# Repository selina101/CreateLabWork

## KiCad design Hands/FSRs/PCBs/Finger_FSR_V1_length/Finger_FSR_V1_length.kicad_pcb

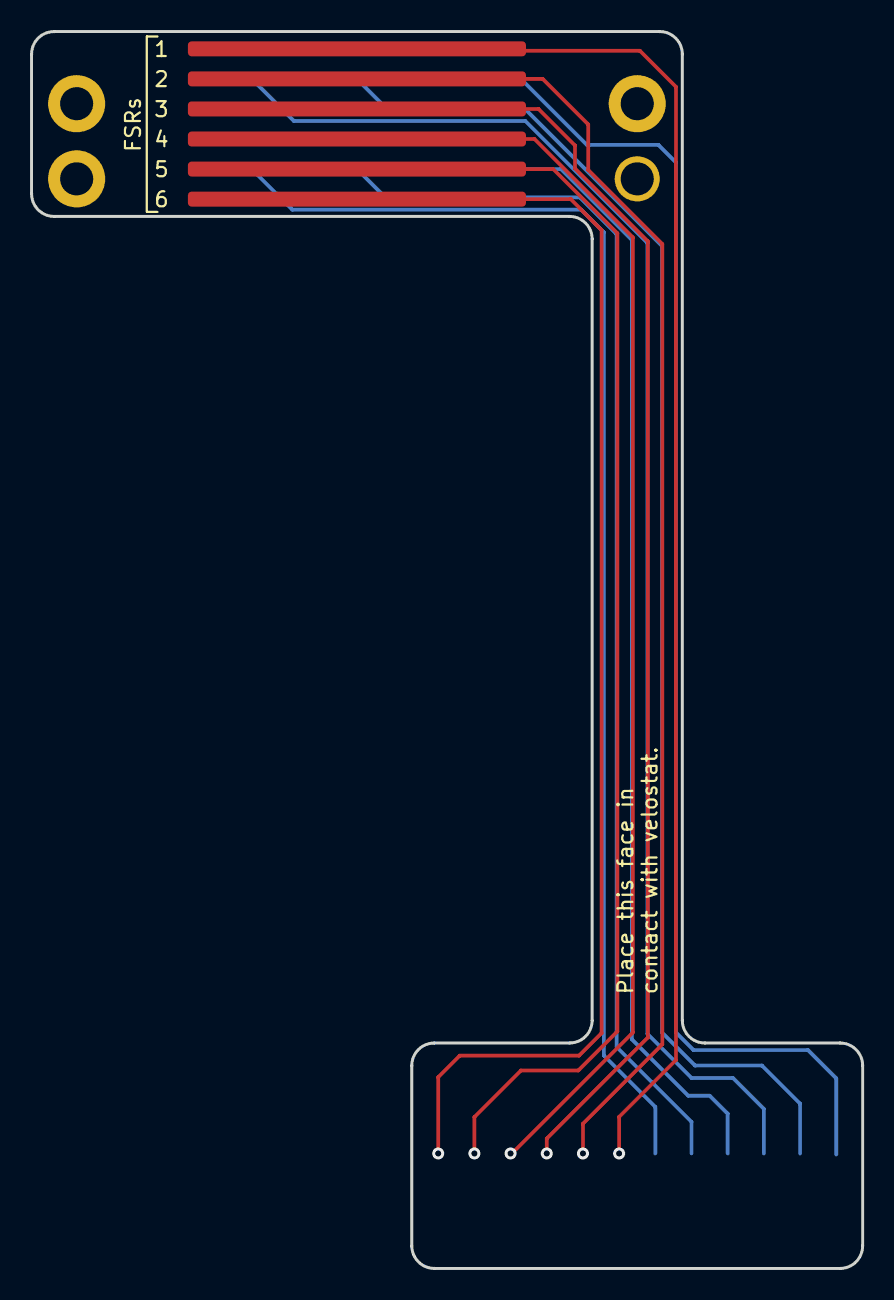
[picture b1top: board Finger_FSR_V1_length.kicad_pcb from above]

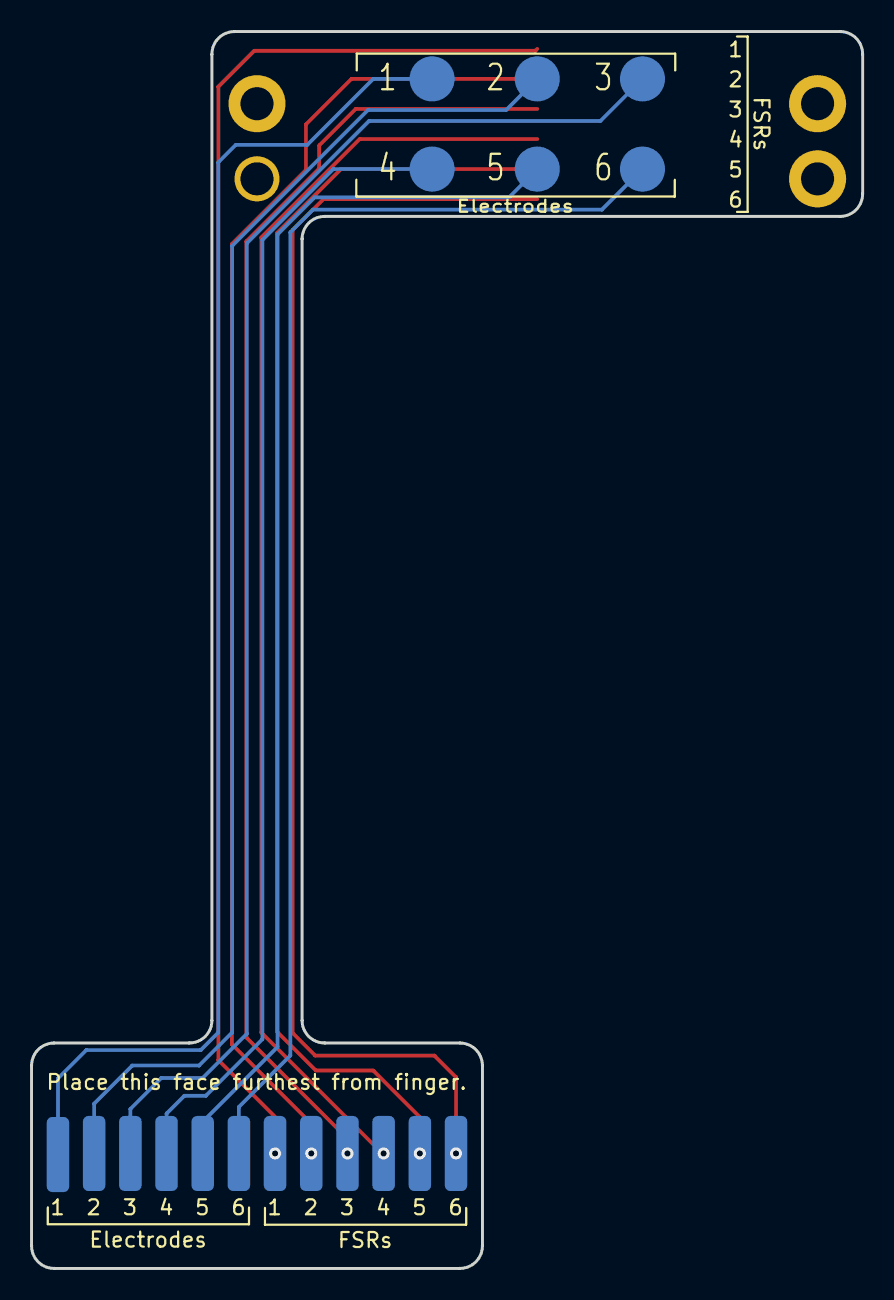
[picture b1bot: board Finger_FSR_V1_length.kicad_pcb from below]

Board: 2 copper layers, 55.3 x 82.3 mm, 28 parts (18 on the bottom side), 12 nets.

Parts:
E1, E2, E3, E4, E5, E6: Finger_FSR_V1_Length
E7, E8, E9, E10, E11, E12: Electrode
H1, H2, H3, H4: MountingHole_Pad; MountingHole_2.2mm_M2_DIN965_Pad
U1, U2, U3, U4, U5, U6: pad
U7, U8, U9, U10, U11, U12: pad; Long_pad

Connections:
unnamed: E1.1, U1.1
unnamed: E2.1, U2.1
unnamed: E3.1, U3.1
unnamed: E4.1, U4.1
unnamed: E5.1, U5.1
unnamed: E6.1, U6.1
unnamed: E7.1, U7.1
unnamed: E8.1, U8.1
unnamed: E9.1, U9.1
unnamed: E10.1, U10.1
unnamed: E11.1, U11.1
unnamed: E12.1, U12.1

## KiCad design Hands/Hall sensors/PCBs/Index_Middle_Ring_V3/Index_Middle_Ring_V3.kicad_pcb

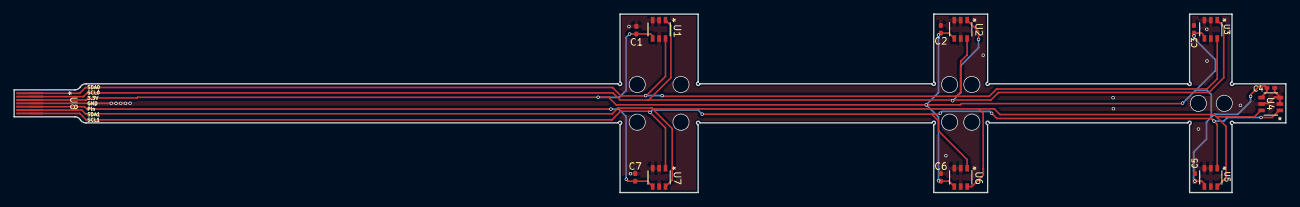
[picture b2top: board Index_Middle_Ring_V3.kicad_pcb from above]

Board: 2 copper layers, 188.9 x 26.5 mm, 15 parts (0 on the bottom side), 7 nets.

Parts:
C1, C2, C3, C4, C5, C6, C7: 0.1uF; C_0402_1005Metric_Pad0.74x0.62mm_HandSolder
U1, U2, U3, U4, U5, U6, U7: TMAG5273A2QDBVR; TMAG5273A2
U8: 7Pin_FingerConnector_for 0527450797

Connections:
+3V3: C1.1, C2.1, C3.1, C4.1, C5.1, C6.1, U1.4 (VCC), U2.4 (VCC), U3.4 (VCC), U4.4 (VCC), U5.4 (VCC), U6.4 (VCC), U8.3
/Pin: C7.1, U7.4 (VCC), U8.5
/SCL0: U1.1 (SCL), U2.1 (SCL), U3.1 (SCL), U8.2
/SCL1: U4.1 (SCL), U5.1 (SCL), U6.1 (SCL), U7.1 (SCL), U8.7
/SDA0: U1.6 (SDA), U2.6 (SDA), U3.6 (SDA), U8.1
/SDA1: U4.6 (SDA), U5.6 (SDA), U6.6 (SDA), U7.6 (SDA), U8.6
GND: C1.2, C2.2, C3.2, C4.2, C5.2, C6.2, C7.2, U1.2 (GND), U1.3 (GND(TEST)), U1.5 (*INT), U2.2 (GND), U2.3 (GND(TEST)), U2.5 (*INT), U3.2 (GND), U3.3 (GND(TEST)), U3.5 (*INT), U4.2 (GND), U4.3 (GND(TEST)), U4.5 (*INT), U5.2 (GND), U5.3 (GND(TEST)), U5.5 (*INT), U6.2 (GND), U6.3 (GND(TEST)), U6.5 (*INT), U7.2 (GND), U7.3 (GND(TEST)), U7.5 (*INT), U8.4

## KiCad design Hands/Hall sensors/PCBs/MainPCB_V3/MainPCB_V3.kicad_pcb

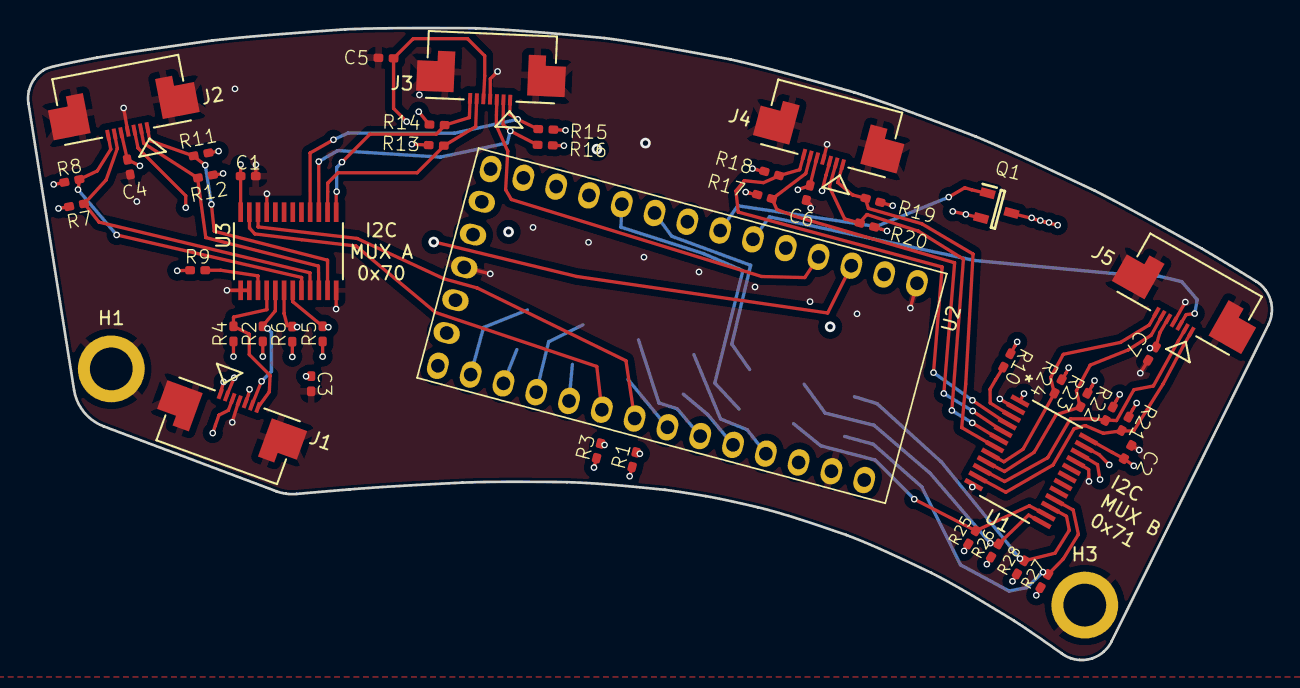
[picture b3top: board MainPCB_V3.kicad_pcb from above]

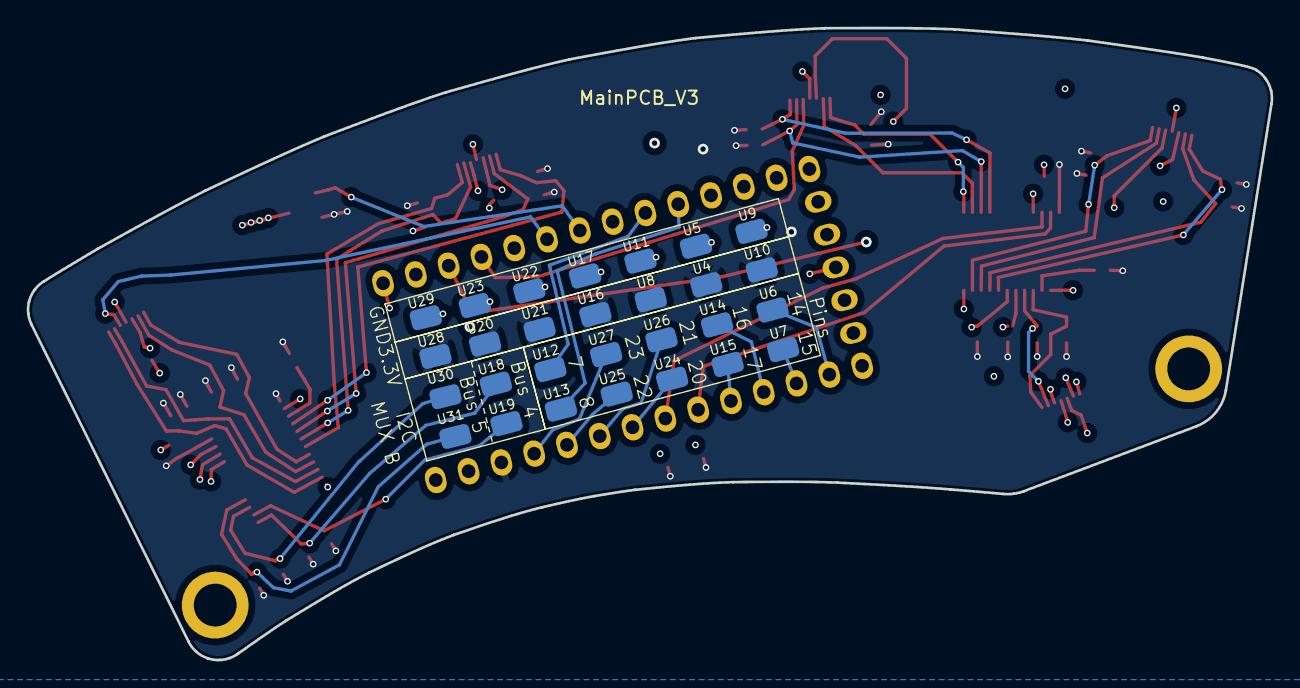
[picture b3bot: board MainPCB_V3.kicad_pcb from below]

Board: 4 copper layers, 93.1 x 47.3 mm, 74 parts (28 on the bottom side), 47 nets.

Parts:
C1, C2: 1uF; 0402_HandSolder
C3, C4, C5, C6, C7: 22uF; 0402_HandSolder
H1, H3: MountingHole_Pad; MountingHole_3.2mm_M3_DIN965_Pad
J1, J2, J3, J4, J5: Molex_0527450797
Q1: DMP31D0U-7
R1, R2, R3, R4, R5, R6, R7, R8, R9, R10, R11, R12, R13, R14, R15, R16, R17, R18, R19, R20, R21, R22, R23, R24, R25, R26, R27, R28: 10k; 0402_HandSolder
U1, U3: TCA9548APWR
U2: Teensy_4.0
U4, U5, U6, U7, U8, U9, U10, U11, U12, U13, U14, U15, U16, U17, U18, U19, U20, U21, U22, U23, U24, U25, U26, U27, U28, U29, U30, U31: pad

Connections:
+3V3: C1.1, C2.1, Q1.2 (S), R1.1, R2.1, R3.1, R4.1, R5.1, R6.1, R7.1, R8.1, R9.1, R10.1, R11.1, R12.1, R13.1, R14.1, R15.1, R16.1, R17.1, R18.1, R19.1, R20.1, R21.1, R22.1, R23.1, R24.1, R25.1, R26.1, R27.1, R28.1, U1.1 (A0), U1.24 (VCC), U2.3.3V_2, U3.24 (VCC), U4.1, U8.1, U10.1, U16.1, U20.1, U21.1, U28.1
/A0: U2.14, U6.1
/A1: U2.15, U7.1
/A2: U2.16, U14.1
/A3: U2.17, U15.1
/A6: U2.20, U24.1
/A7: U2.21, U26.1
/A8: U2.22, U25.1
/A9: U2.23, U27.1
/Gate: Q1.1 (G), U2.5
/IO0: J1.3, U2.0
/IO1: J2.3, U2.1
/IO2: J3.3, U2.2
/IO3: J4.3, U2.3
/IO4: J5.3, U2.4
/PMOS_output: C3.1, C4.1, C5.1, C6.1, C7.1, J1.5, J2.5, J3.5, J4.5, J5.5, Q1.3 (D)
/RX2: U2.7, U12.1
/SCL0: J1.6, R2.2, U3.5 (SC0)
/SCL1: J1.1, R5.2, U3.7 (SC1)
/SCL2: J2.6, R7.2, U3.9 (SC2)
/SCL3: J2.1, R11.2, U3.11 (SC3)
/SCL4: J3.6, R13.2, U3.14 (SC4)
/SCL5: J3.1, R15.2, U3.16 (SC5)
/SCL_B0: J4.6, R17.2, U1.5 (SC0)
/SCL_B1: J4.1, R19.2, U1.7 (SC1)
/SCL_B2: J5.6, R23.2, U1.9 (SC2)
/SCL_B3: J5.1, R21.2, U1.11 (SC3)
/SCL_B4: R25.2, U1.14 (SC4), U19.1
/SCL_B5: R27.2, U1.16 (SC5), U31.1
/SCL_IN: R1.2, U1.22 (SCL), U2.19, U3.22 (SCL)
/SDA0: J1.7, R4.2, U3.4 (SD0)
/SDA1: J1.2, R6.2, U3.6 (SD1)
/SDA2: J2.7, R8.2, U3.8 (SD2)
/SDA3: J2.2, R12.2, U3.10 (SD3)
/SDA4: J3.7, R14.2, U3.13 (SD4)
/SDA5: J3.2, R16.2, U3.15 (SD5)
/SDA_B0: J4.7, R18.2, U1.4 (SD0)
/SDA_B1: J4.2, R20.2, U1.6 (SD1)
/SDA_B2: J5.7, R24.2, U1.8 (SD2)
/SDA_B3: J5.2, R22.2, U1.10 (SD3)
/SDA_B4: R26.2, U1.13 (SD4), U18.1
/SDA_B5: R28.2, U1.15 (SD5), U30.1
/SDA_IN: R3.2, U1.23 (SDA), U2.18, U3.23 (SDA)
/TX2: U2.8, U13.1
GND: C1.2, C2.2, C3.2, C4.2, C5.2, C6.2, C7.2, H1.1, H3.1, J1.4, J1.P1, J1.P2, J2.4, J2.P1, J2.P2, J3.4, J3.P1, J3.P2, J4.4, J4.P1, J4.P2, J5.4, J5.P1, J5.P2, U1.2 (A1), U1.12 (GND), U1.21 (A2), U2.G1, U2.G2, U2.G3, U3.1 (A0), U3.2 (A1), U3.12 (GND), U3.21 (A2), U5.1, U9.1, U11.1, U17.1, U22.1, U23.1, U29.1
unnamed: R10.2, U1.3 (*RESET)
unnamed: R9.2, U3.3 (*RESET)
